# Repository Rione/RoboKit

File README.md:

# RoboKit 環境構築

<aside>
👉 目標：自分のPCにRoboKit用のプログラムを持ってきて、VSCodeに拡張機能のPlatformIOをinstallする。

</aside>

# 自分のPCにRoboKitのプログラムを持ってくる

↓これを開く

[GitHub - Rione/RoboKit](https://github.com/Rione/RoboKit/tree/master)

## 2つの方法がある

- ファイルをダウンロードする
- ファイル(リポジトリ)をクローンする

## 方法1

`<>Code`から、`Download ZIP`でZIPファイルをダウンロード。→ 展開する。

RoboKit-masterというフォルダがDownloadsフォルダに保存されている

## 方法2

今回はDownloadsフォルダにRoboKitのフォルダを複製する
↓一行ずつターミナルで実行

```bash
cd
cd Downloads
git clone https://github.com/Rione/RoboKit.git
```

※ ちなみに…  `git clone (URL)` で既存のリポジトリを自分のPC内に複製できる

RoboKitというフォルダがDownloadsフォルダに保存されている

# VSCodeのインストール

# VSCodeにPlatform IOをinstallする

サイドバーの拡張機能（ブロックのようなアイコン）をクリック

上の検索バーにPlatform IOと入力

これをinstall(インストールボタンをクリックすることで入ります)

サイドバーからPlatform IOを選択して、Quick Access > PIO Home > Projects & Configure を選択すると、上の画面が出てくる。

画面右側のOpenを押すと、RoboKitのテスト用フォルダが開かれる

---

「出力」でいろいろ流れて、最終的に上の画面になったら成功！

企画で使用するファイルは上画面で表示されている、main.cppだけです。

余力のある人は、実際にビルドができるか確認してもらえると嬉しいです。
下の青いラインに並んでいる、✅を押すとビルド、→を押すと書き込みができます。

以上でPCの事前準備はおしまいですが、分からないことがあれば遠慮せずに聞いてください！

---

# Windowsの諸注意

WindowsにGitが入っている必要があります．Gitのインストールをしてください．(自分で調べてください)

### Gitが入っているかの確認

ターミナルで次のコマンドを打ってみてください．

```
git help
```

と打って反応があればGitが入っている証拠です．

- ターミナルで期待される反応はこんな感じです．
    
    ```
    git help
    usage: git [--version] [--help] [-C <path>] [-c <name>=<value>]
               [--exec-path[=<path>]] [--html-path] [--man-path] [--info-path]
               [-p | --paginate | -P | --no-pager] [--no-replace-objects] [--bare]
               [--git-dir=<path>] [--work-tree=<path>] [--namespace=<name>]
               [--super-prefix=<path>] [--config-env=<name>=<envvar>]
               <command> [<args>]
    
    These are common Git commands used in various situations:
    
    start a working area (see also: git help tutorial)
       clone     Clone a repository into a new directory
       init      Create an empty Git repository or reinitialize an existing one
    
    work on the current change (see also: git he
    ```

### RoboKitのファイルの初期化時にエラーが出る(longpathエラー)

- WindowsのgitはMacと違い，longpath = falseになっているので，trueにしましょう
- WindowsのGitの入っているPCで以下のコマンドを実行してください．

```
git config --system core.longpaths true
```

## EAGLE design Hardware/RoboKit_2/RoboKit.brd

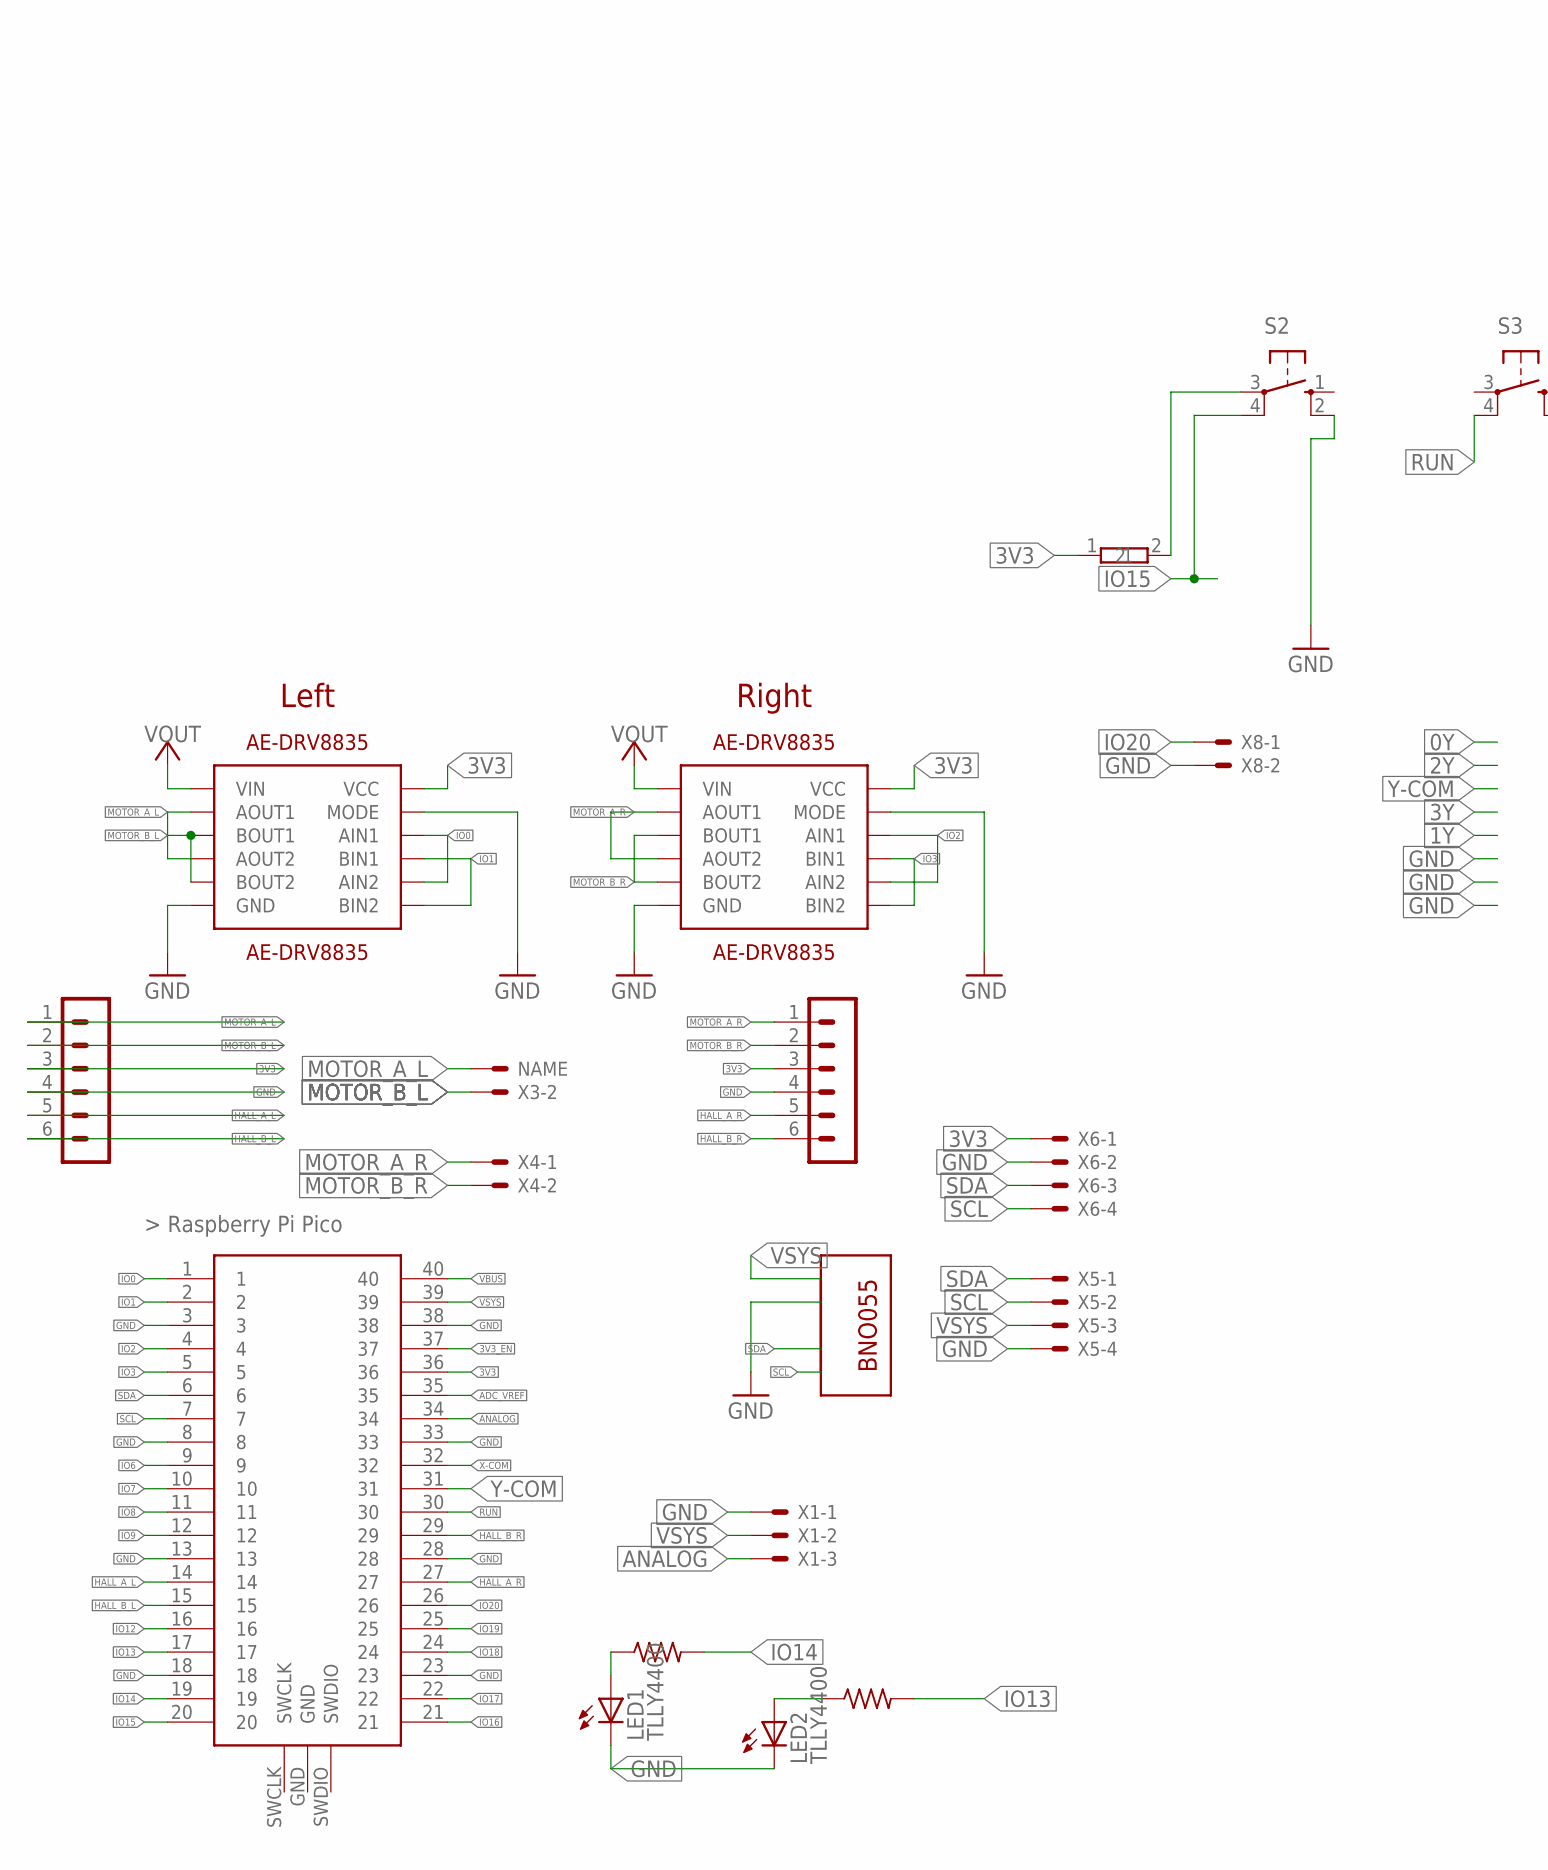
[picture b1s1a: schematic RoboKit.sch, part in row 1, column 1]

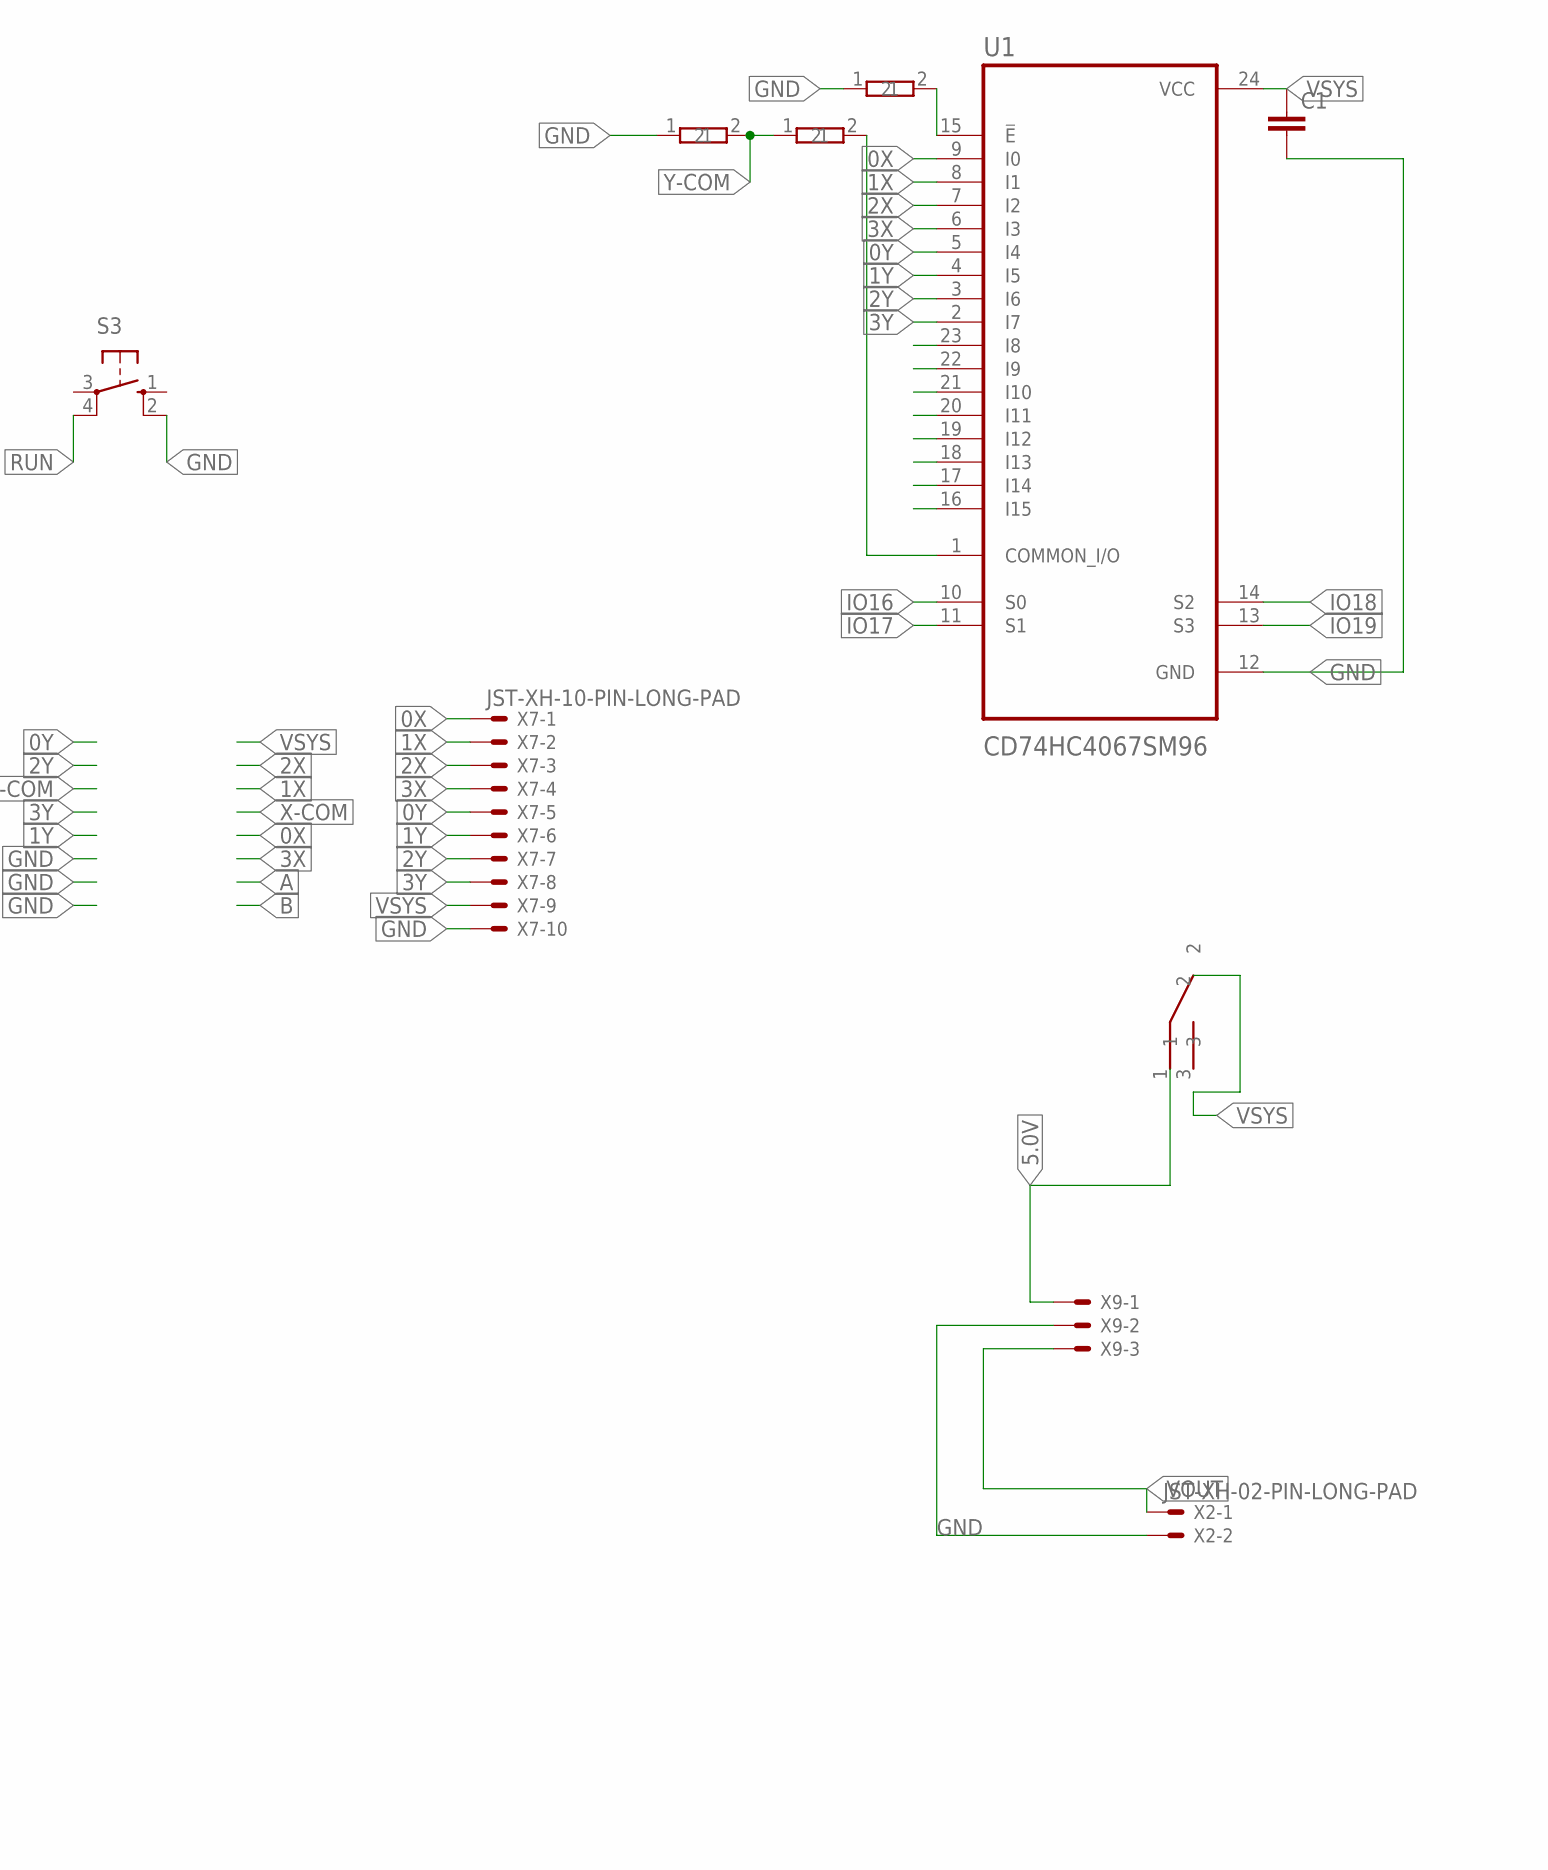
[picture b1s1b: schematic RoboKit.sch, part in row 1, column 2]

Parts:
C1: C-EU025-024X044; C025-024X044
CONNECTOR1, CONNECTOR4, CONNECTOR5, CONNECTOR6: RESISTER; RESISTER_SOCKET
LED1, LED2: TLLY4400; LED3MM
P1, P2: B6B-PH-K
R2, R3: R-US_R0603; R0603
S2: 40-XX; B3F-40XX
S3: 10-XX; B3F-10XX
U1: CD74HC4067SM96; SOP65P780X200-24N
U$1: RASPBERRY-PI-PICO_TH; FT_RASPBERRY-PI-PICO_TH
U$2, U$3: AE-DRV8835
U$4: AE-BNO055-BO
U$8: SW
X1, X9: JST-XH-03-PIN-LONG-PAD; JST-XH-03-PACKAGE-LONG-PAD
X2, X3, X4, X8: JST-XH-02-PIN-LONG-PAD; JST-XH-02-PACKAGE-LONG-PAD
X5, X6: JST-XH-04-PIN-LONG-PAD; JST-XH-04-PACKAGE-LONG-PAD
X7: JST-XH-10-PIN-LONG-PAD; JST-XH-10-PACKAGE-LONG-PAD

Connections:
0X: U1.9 (I0), X7.1
0Y: U1.5 (I4), X7.5
1X: U1.8 (I1), X7.2
1Y: U1.4 (I5), X7.6
2X: U1.7 (I2), X7.3
2Y: U1.3 (I6), X7.7
3V3: CONNECTOR1.1, P1.3, P2.3, U$1.36, U$2.VCC, U$3.VCC, X6.1
3V3_EN: U$1.37
3X: U1.6 (I3), X7.4
3Y: U1.2 (I7), X7.8
5.0V: U$8.1, X9.1
ADC_VREF: U$1.35
ANALOG: U$1.34, X1.3
GND: C1.2, CONNECTOR5.1, CONNECTOR6.1, LED1.K (C), LED2.K (C), P1.4, P2.4, S2.2 (S1), S3.2 (S1), U1.12 (GND), U$1.3, U$1.8, U$1.13, U$1.18, U$1.23, U$1.28, U$1.33, U$1.38, U$2.GND, U$2.MODE, U$3.GND, U$3.MODE, U$4.GND, X1.1, X2.2, X5.4, X6.2, X7.10, X8.2, X9.2
HALL_A_L: P2.5, U$1.14
HALL_A_R: P1.5, U$1.27
HALL_B_L: P2.6, U$1.15
HALL_B_R: P1.6, U$1.29
IO0: U$1.1, U$2.INA1 (AIN1), U$2.INA2 (AIN2)
IO1: U$1.2, U$2.INB1 (BIN1), U$2.INB2 (BIN2)
IO2: U$1.4, U$3.INA1 (AIN1), U$3.INA2 (AIN2)
IO3: U$1.5, U$3.INB1 (BIN1), U$3.INB2 (BIN2)
IO6: U$1.9
IO7: U$1.10
IO8: U$1.11
IO9: U$1.12
IO12: U$1.16
IO13: R3.2, U$1.17
IO14: R2.2, U$1.19
IO15: S2.4 (P1), U$1.20
IO16: U1.10 (S0), U$1.21
IO17: U1.11 (S1), U$1.22
IO18: U1.14 (S2), U$1.24
IO19: U1.13 (S3), U$1.25
IO20: U$1.26, X8.1
MOTOR_A_L: P2.1, U$2.AOUT1, U$2.AOUT2, X3.1
MOTOR_A_R: P1.1, U$3.AOUT1, U$3.AOUT2, X4.1
MOTOR_B_L: P2.2, U$2.BOUT1, U$2.BOUT2, X3.2
MOTOR_B_R: P1.2, U$3.BOUT1, U$3.BOUT2, X4.2
unnamed: LED1.A, R2.1
unnamed: CONNECTOR1.2, S2.3
unnamed: LED2.A, R3.1
unnamed: CONNECTOR6.2, U1.15 (!E)
unnamed: CONNECTOR4.2, U1.1 (COMMON_I/O)
RUN: S3.4 (P1), U$1.30
SCL: U$1.7, U$4.SCL, X5.2, X6.4
SDA: U$1.6, U$4.SDA, X5.1, X6.3
VBUS: U$1.40
VOUT: U$2.VIN, U$3.VIN, X2.1, X9.3
VSYS: C1.1, U1.24 (VCC), U$1.39, U$4.VIN, U$8.2, X1.2, X5.3, X7.9
X-COM: U$1.32
Y-COM: CONNECTOR4.1, CONNECTOR5.2, U$1.31

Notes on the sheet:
Right
Left

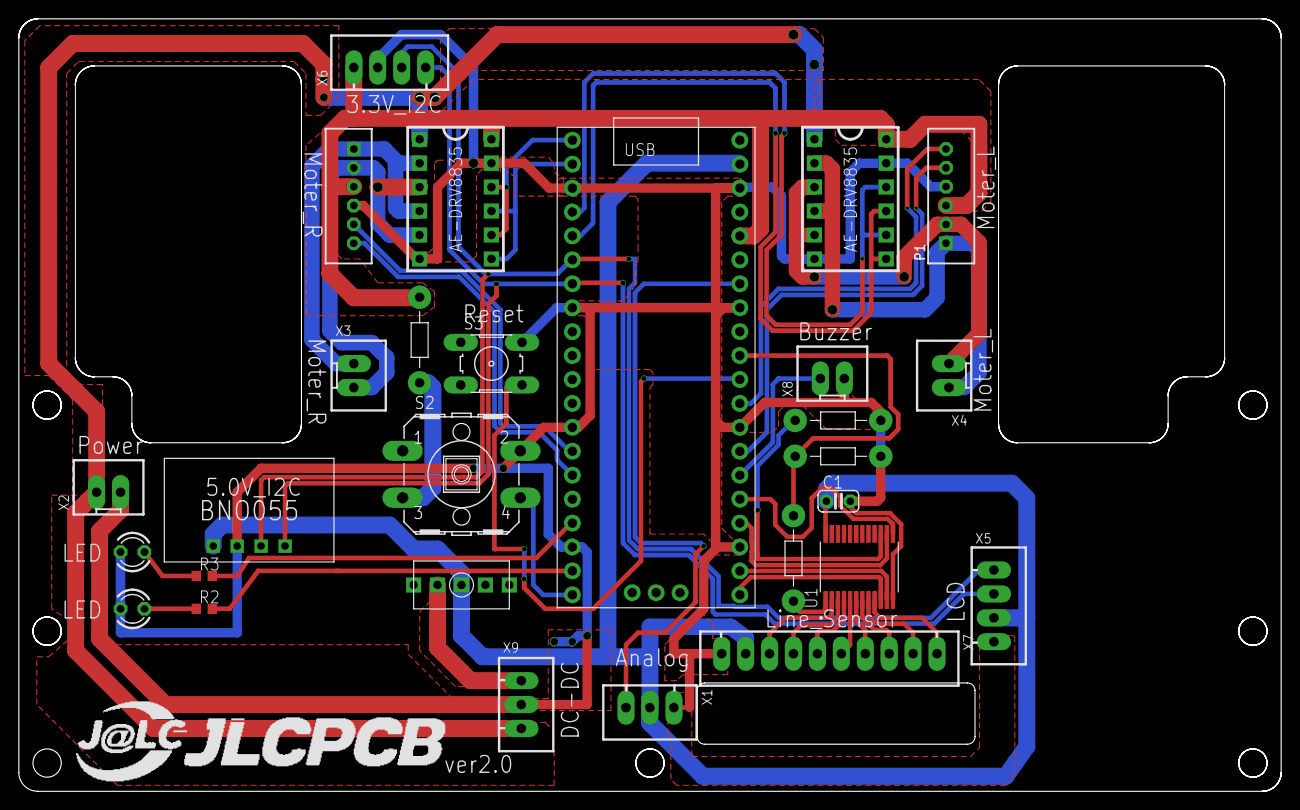
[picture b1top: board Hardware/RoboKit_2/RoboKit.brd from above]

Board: 2 copper layers, 134.0 x 82.0 mm, 28 parts (0 on the bottom side), 43 nets.

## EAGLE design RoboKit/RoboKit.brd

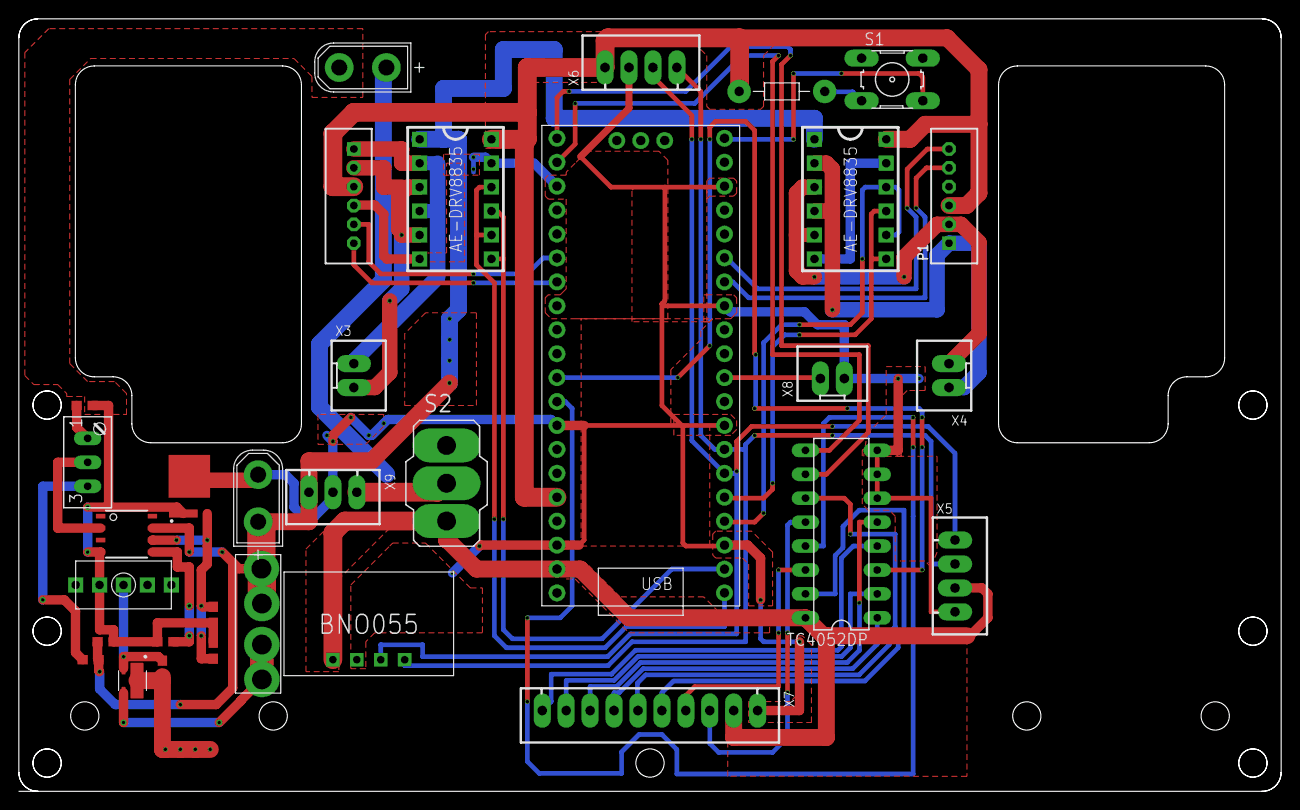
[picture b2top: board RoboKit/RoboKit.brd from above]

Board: 2 copper layers, 134.0 x 82.0 mm, 32 parts (0 on the bottom side), 43 nets.

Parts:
C2, C11: 1uF; C0603
C7: 0.1uF; 0603
CON1, CON2: XT30UPB-M
CONNECTOR1: RESISTER; RESISTER_SOCKET
P1, P2: B6B-PH-K
R1, R4: 20k; 0603
R2: 10k; 0603
R3: 2k; 0603
R5: 1k; S64W
S1: B3F-10XX
S2: 320-916
TC4052DP: DIL16
U1: SSM6J808R
U$1: RASPBERRY-PI-PICO_TH; FT_RASPBERRY-PI-PICO_TH
U$2, U$3: AE-DRV8835
U$4: AE-BNO055-BO
U$5: M51957; SOP-8
U$6: BSC093N04LSGATMA1; MOSFET_BSC093N04LSGATMA1
U$7: FUSE
U$9: SW
X3, X4, X8: JST-XH-02-PIN-LONG-PAD; JST-XH-02-PACKAGE-LONG-PAD
X5, X6: JST-XH-04-PIN-LONG-PAD; JST-XH-04-PACKAGE-LONG-PAD
X7: JST-XH-10-PIN-LONG-PAD; JST-XH-10-PACKAGE-LONG-PAD
X9: JST-XH-03-PIN-LONG-PAD; JST-XH-03-PACKAGE-LONG-PAD

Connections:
0X: TC4052DP.12, X7.3
0Y: TC4052DP.1, X7.7
1X: TC4052DP.14, X7.4
1Y: TC4052DP.5, X7.8
2X: TC4052DP.15, X7.5
2Y: TC4052DP.2, X7.9
3V3: CONNECTOR1.1, P1.3, P2.3, U$1.36, U$2.VCC, U$3.VCC, X6.1
3X: TC4052DP.11, X7.6
3Y: TC4052DP.4, X7.10
5.0V: S2.2, X9.1
A: TC4052DP.10, U$1.21
B: TC4052DP.9, U$1.22
GND: CON1.-, P1.4, P2.4, S1.2, TC4052DP.6, TC4052DP.7, TC4052DP.8, U$1.3, U$1.8, U$1.13, U$1.18, U$1.23, U$1.28, U$1.33, U$1.38, U$2.GND, U$2.MODE, U$3.GND, U$3.MODE, U$4.GND, U$6.D, X5.4, X6.2, X7.1, X8.2, X9.2
GND_IN: C2.2, C7.1, C11.2, CON2.-, R2.1, R3.2, U$5.GND, U$6.S, U$9.1
HALL_A_L: P2.5, U$1.26
HALL_A_R: P1.5, U$1.14
HALL_B_L: P2.6, U$1.27
HALL_B_R: P1.6, U$1.15
IO0: U$1.1, U$2.INA1, U$2.INA2
IO1: U$1.2, U$2.INB1, U$2.INB2
IO2: U$1.4, U$3.INA1, U$3.INA2
IO3: U$1.5, U$3.INB1, U$3.INB2
IO7: U$1.10, X8.1
IO15: S1.4, U$1.20
MOTOR_A_L: P2.1, U$2.AOUT1, U$2.AOUT2, X3.1
MOTOR_A_R: P1.1, U$3.AOUT1, U$3.AOUT2, X4.1
MOTOR_B_L: P2.2, U$2.BOUT1, U$2.BOUT2, X3.2
MOTOR_B_R: P1.2, U$3.BOUT1, U$3.BOUT2, X4.2
unnamed: R5.S, U$5.IN
unnamed: R3.1, R5.A
unnamed: R1.1, R5.E
unnamed: CONNECTOR1.2, S1.3
unnamed: C11.1, U$5.C
unnamed: C7.2, R2.2, U$5.OUT, U$6.GATE
unnamed: R4.1, U1.G, U$9.2
SCL: U$1.7, U$4.SCL, X5.2, X6.4
SDA: U$1.6, U$4.SDA, X5.1, X6.3
VIN: CON2.+, R4.2, U1.D
VOUT: C2.1, CON1.+, R1.2, U$2.VIN, U$3.VIN, U$5.V, U$7.1, U$7.2, X9.3
VSYS: S2.3, TC4052DP.16, U$1.39, U$4.VIN, X5.3, X7.2
V_HIGH: U1.S, U$7.3, U$7.4
X-COM: TC4052DP.13, U$1.32
Y-COM: TC4052DP.3, U$1.31

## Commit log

2023-02-03 add cad
2023-02-12 保護回路を描いた
2023-02-28 add I2C
2023-03-05 make_circuit
2023-03-07 make_okunishi_1
2023-03-10 回路図の完成
2023-03-10 ボードのグランド以外を配置
2023-03-12 線を斜めに配置
2023-03-13 保護回路の配線を設定
2023-03-14 一応完成
2023-03-16 gitignoreを設定
2023-03-16 テスト2回目
2023-03-16 テスト3回目
2023-03-16 テスト_4
2023-03-16 テスト5回目
2023-03-16 テスト_6
2023-03-16 テスト7
2023-03-16 テスト8
2023-03-16 テスト10
2023-03-18 信号線の太さを変更
2023-03-19 ポリゴンの範囲を拡大
2023-03-20 ポリゴンの面積を拡大
2023-03-21 ビアの位置を修正
2023-03-21 Air wireを修正
2023-03-22 モーター部分の太さを修正
2023-03-28 CAMファイルを追加
2023-04-20 ver2.0の作成
2023-04-20 大半のボード配線を変更
2023-04-21 とりあえず完成！
2023-04-21 かんせい
2023-04-21 シルク追加
2023-04-22 マルチプレクサの電源回り付近を修正
2023-04-24 ロゴマークを追加
2023-05-01 5回目課題
2023-06-10 XH10ピンが刺さらない不具合を修正し、アナログ出力の印刷が逆になっていたのを修正し、ver2.0のシルクを追加
2023-06-10 DRC通過
2023-06-12 :warning: Fix position of JLCPCB logo
2023-06-12 ⚠️ Fix position of JLCPCB logo
    # ==== Emojis ====
    # ✨ :sparkles: Add new feature
    # ✅ :white_check_mark: Update existing feature (not bug)
    # ⚠️ :warning: Fix bug/error
    # 🔥 :fire: Remove files or features
    # ✏️ :pencil2: Fix typos
2023-06-26 :pencil2: Make Hardware folder
    # ==== Emojis ====
    # ✨ :sparkles: Add new feature
    # ✅ :white_check_mark: Update existing feature (not bug)
    # ⚠️ :warning: Fix bug/error
    # 🔥 :fire: Remove files or features
    # ✏️ :pencil2: Fix typos
2023-06-26 :fire: remove backup files
    # ==== Emojis ====
    # ✨ :sparkles: Add new feature
    # ✅ :white_check_mark: Update existing feature (not bug)
    # ⚠️ :warning: Fix bug/error
    # 🔥 :fire: Remove files or features
    # ✏️ :pencil2: Fix typos
2023-06-26 :tada: create robokit Project files with PIO
    # ==== Emojis ====
    # ✨ :sparkles: Add new feature
    # ✅ :white_check_mark: Update existing feature (not bug)
    # ⚠️ :warning: Fix bug/error
    # 🔥 :fire: Remove files or features
    # ✏️ :pencil2: Fix typos
2023-06-26 :sparkles: add mbed Like Simple IO-Wrapper
    # ==== Emojis ====
    # ✨ :sparkles: Add new feature
    # ✅ :white_check_mark: Update existing feature (not bug)
    # ⚠️ :warning: Fix bug/error
    # 🔥 :fire: Remove files or features
    # ✏️ :pencil2: Fix typos
2023-06-26 :sparkles: ラインセンサとモータに関するメソッドの追加
    # ==== Emojis ====
    # ✨ :sparkles: Add new feature
    # ✅ :white_check_mark: Update existing feature (not bug)
    # ⚠️ :warning: Fix bug/error
    # 🔥 :fire: Remove files or features
    # ✏️ :pencil2: Fix typos
2023-06-26 :sparkles: Add SwitchObserver
    # ==== Emojis ====
    # ✨ :sparkles: Add new feature
    # ✅ :white_check_mark: Update existing feature (not bug)
    # ⚠️ :warning: Fix bug/error
    # 🔥 :fire: Remove files or features
    # ✏️ :pencil2: Fix typos
2023-06-26 :sparkles: SWが押されたらLoopが走るように変更
    # ==== Emojis ====
    # ✨ :sparkles: Add new feature
    # ✅ :white_check_mark: Update existing feature (not bug)
    # ⚠️ :warning: Fix bug/error
    # 🔥 :fire: Remove files or features
    # ✏️ :pencil2: Fix typos
2023-06-26 :pencil2: fix gitignore
    # ==== Emojis ====
    # ✨ :sparkles: Add new feature
    # ✅ :white_check_mark: Update existing feature (not bug)
    # ⚠️ :warning: Fix bug/error
    # 🔥 :fire: Remove files or features
    # ✏️ :pencil2: Fix typos
2023-06-26 :fire: remove .DS_Store
    # ==== Emojis ====
    # ✨ :sparkles: Add new feature
    # ✅ :white_check_mark: Update existing feature (not bug)
    # ⚠️ :warning: Fix bug/error
    # 🔥 :fire: Remove files or features
    # ✏️ :pencil2: Fix typos
2023-06-26 :sparkles: ラインセンサをまとめて読むメソッドを追加
    # ==== Emojis ====
    # ✨ :sparkles: Add new feature
    # ✅ :white_check_mark: Update existing feature (not bug)
    # ⚠️ :warning: Fix bug/error
    # 🔥 :fire: Remove files or features
    # ✏️ :pencil2: Fix typos
2023-06-26 :sparkles: サンプルコードを追加
    # ==== Emojis ====
    # ✨ :sparkles: Add new feature
    # ✅ :white_check_mark: Update existing feature (not bug)
    # ⚠️ :warning: Fix bug/error
    # 🔥 :fire: Remove files or features
    # ✏️ :pencil2: Fix typos
2023-06-26 :pencil2: Doxygen用コメントを追加
    # ==== Emojis ====
    # ✨ :sparkles: Add new feature
    # ✅ :white_check_mark: Update existing feature (not bug)
    # ⚠️ :warning: Fix bug/error
    # 🔥 :fire: Remove files or features
    # ✏️ :pencil2: Fix typos
2023-06-26 :sparkles: モータの回転方向を設定するsetMotorCWを追加
    # ==== Emojis ====
    # ✨ :sparkles: Add new feature
    # ✅ :white_check_mark: Update existing feature (not bug)
    # ⚠️ :warning: Fix bug/error
    # 🔥 :fire: Remove files or features
    # ✏️ :pencil2: Fix typos
2023-06-26 :sparkles: ToF(VL53L0X)の読み取りメソッドを追加
    # ==== Emojis ====
    # ✨ :sparkles: Add new feature
    # ✅ :white_check_mark: Update existing feature (not bug)
    # ⚠️ :warning: Fix bug/error
    # 🔥 :fire: Remove files or features
    # ✏️ :pencil2: Fix typos
2023-06-26 :sparkles: BNO055でEuler angle(degree)の読み取りメソッドの追加
    # ==== Emojis ====
    # ✨ :sparkles: Add new feature
    # ✅ :white_check_mark: Update existing feature (not bug)
    # ⚠️ :warning: Fix bug/error
    # 🔥 :fire: Remove files or features
    # ✏️ :pencil2: Fix typos
2023-06-26 :sparkles: ラインセンサの値を表示するメソッドを追加
    # ==== Emojis ====
    # ✨ :sparkles: Add new feature
    # ✅ :white_check_mark: Update existing feature (not bug)
    # ⚠️ :warning: Fix bug/error
    # 🔥 :fire: Remove files or features
    # ✏️ :pencil2: Fix typos
2023-06-26 :pencil2: fix isWhiteの場所 / printLineからprintLinesに変更
    # ==== Emojis ====
    # ✨ :sparkles: Add new feature
    # ✅ :white_check_mark: Update existing feature (not bug)
    # ⚠️ :warning: Fix bug/error
    # 🔥 :fire: Remove files or features
    # ✏️ :pencil2: Fix typos
2023-06-26 :pencil2: printLinesにデフォルト引数を追加
    # ==== Emojis ====
    # ✨ :sparkles: Add new feature
    # ✅ :white_check_mark: Update existing feature (not bug)
    # ⚠️ :warning: Fix bug/error
    # 🔥 :fire: Remove files or features
    # ✏️ :pencil2: Fix typos
2023-06-27 :memo: LED Blink
    # ==== Emojis ====
    # ✨ :sparkles: Add new feature
    # ✅ :white_check_mark: Update existing feature (not bug)
    # ⚠️ :warning: Fix bug/error
    # 🔥 :fire: Remove files or features
    # ✏️ :pencil2: Fix typos
2023-06-27 :memo: Doxygenでドキュメント生成した
    # ==== Emojis ====
    # ✨ :sparkles: Add new feature
    # ✅ :white_check_mark: Update existing feature (not bug)
    # ⚠️ :warning: Fix bug/error
    # 🔥 :fire: Remove files or features
    # ✏️ :pencil2: Fix typos
2023-06-27 :sparkles: Earlephilhower support on PlatformIO
    # ==== Emojis ====
    # ✨ :sparkles: Add new feature
    # ✅ :white_check_mark: Update existing feature (not bug)
    # ⚠️ :warning: Fix bug/error
    # 🔥 :fire: Remove files or features
    # ✏️ :pencil2: Fix typos
2023-06-27 :sparkles: スイッチ押したらLoopが走るようになった
    # ==== Emojis ====
    # ✨ :sparkles: Add new feature
    # ✅ :white_check_mark: Update existing feature (not bug)
    # ⚠️ :warning: Fix bug/error
    # 🔥 :fire: Remove files or features
    # ✏️ :pencil2: Fix typos
2023-06-27 :white_check_mark: Motor Test
    # ==== Emojis ====
    # ✨ :sparkles: Add new feature
    # ✅ :white_check_mark: Update existing feature (not bug)
    # ⚠️ :warning: Fix bug/error
    # 🔥 :fire: Remove files or features
    # ✏️ :pencil2: Fix typos
2023-06-27 :white_check_mark: Line Sensor Test
    # ==== Emojis ====
    # ✨ :sparkles: Add new feature
    # ✅ :white_check_mark: Update existing feature (not bug)
    # ⚠️ :warning: Fix bug/error
    # 🔥 :fire: Remove files or features
    # ✏️ :pencil2: Fix typos
2023-06-27 :memo: update doxygen
    # ==== Emojis ====
    # ✨ :sparkles: Add new feature
    # ✅ :white_check_mark: Update existing feature (not bug)
    # ⚠️ :warning: Fix bug/error
    # 🔥 :fire: Remove files or features
    # ✏️ :pencil2: Fix typos
2023-06-27 :warning: fix PWM max value 1023 to 255
    # ==== Emojis ====
    # ✨ :sparkles: Add new feature
    # ✅ :white_check_mark: Update existing feature (not bug)
    # ⚠️ :warning: Fix bug/error
    # 🔥 :fire: Remove files or features
    # ✏️ :pencil2: Fix typos
2023-06-27 :memo: Fix Motor CW / CCW
    # ==== Emojis ====
    # ✨ :sparkles: Add new feature
    # ✅ :white_check_mark: Update existing feature (not bug)
    # ⚠️ :warning: Fix bug/error
    # 🔥 :fire: Remove files or features
    # ✏️ :pencil2: Fix typos
2023-06-28 :sparkles: add wait() ,wait_ms()
    # ==== Emojis ====
    # ✨ :sparkles: Add new feature
    # ✅ :white_check_mark: Update existing feature (not bug)
    # ⚠️ :warning: Fix bug/error
    # 🔥 :fire: Remove files or features
    # ✏️ :pencil2: Fix typos
2023-06-28 :warning: fix wait macro
    # ==== Emojis ====
    # ✨ :sparkles: Add new feature
    # ✅ :white_check_mark: Update existing feature (not bug)
    # ⚠️ :warning: Fix bug/error
    # 🔥 :fire: Remove files or features
    # ✏️ :pencil2: Fix typos
2023-06-28 :sparkles: Add OLED LCD with U8g2_Arduino
    add https://github.com/olikraus/U8g2_Arduino library
    # ==== Emojis ====
    # ✨ :sparkles: Add new feature
    # ✅ :white_check_mark: Update existing feature (not bug)
    # ⚠️ :warning: Fix bug/error
    # 🔥 :fire: Remove files or features
2023-06-28 :sparkles: add LCD sample
    # ==== Emojis ====
    # ✨ :sparkles: Add new feature
    # ✅ :white_check_mark: Update existing feature (not bug)
    # ⚠️ :warning: Fix bug/error
    # 🔥 :fire: Remove files or features
    # ✏️ :pencil2: Fix typos
2024-06-28 fix for new lib rule

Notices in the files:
parts and their libraries:
con-jst-ph: Copyright (C) 2016, Bob Starr
SparkFun-Resistors: Licensing: Creative Commons ShareAlike 4.0 International - https://creativecommons.org/licenses/by-sa/4.0
